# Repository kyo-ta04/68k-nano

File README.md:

# 68k nano

A minimal single-board computer based on the venerable ["Texas Cockroach"](https://youtu.be/UaHtGf4aRLs?t=2074)
Motorola 68000 16/32-bit microprocessor.

## Schematic, PCB
Schematic : [KiCanvas](https://kicanvas.org/?github=https%3A%2F%2Fgithub.com%2Fkyo-ta04%2F68k-nano%2Fblob%2FDevelop%2F68000sbc.kicad_sch) , [PDF](./68000sbc_sch.pdf)  
PCB : [KiCanvas](https://kicanvas.org/?github=https%3A%2F%2Fgithub.com%2Fkyo-ta04%2F68k-nano%2Fblob%2FDevelop%2F68000sbc.kicad_pcb) , 
[Gerber files](./production/)  

** I added the schematic and PCB using KiCad 9.0.4  -  kyo-ta04(@DragonballEZ) 15-Sep-2025  

## Features

- 68HC000 processor running at 12MHz
- 1MB RAM
- 64KB ROM
- 16550 UART providing a 5V FTDI serial port
- 44-pin IDE connector for CompactFlash card adapter
- Connector for SparkFun DS3234 real-time clock
- Only two 74HC glue logic chips required

This might be capable of running uClinux, but I haven't tried it!

## Hardware

The 68k nano hardware is simple and straightforward. It can be built on a
breadboard (though there may be stability issues at higher clock speeds).

### Memory map

Due to the minimal address decoding circuitry, accessing certain memory regions
will cause multiple devices to be selected. This should be avoided.

```
$000000-0xFFFF     ROM (repeats 16 times)
$100000-1FFFFF  X  Forbidden (multiple devices selected)
$200000-2FFFFF     ROM (mirror of $000000-0FFFFF)
$300000-$7FFFF  X  Forbidden (multiple devices selected)
$800000-8FFFFF     Open bus (available for expansion)
$900000-9xxxxF     CompactFlash card
$A00000-AxxxxF     UART
$B00000-BFFFFF  X  Forbidden (multiple devices selected)
$C00000-CFFFFF     RAM
$D00000-DFFFFF  X  Forbidden (multiple devices selected)
$E00000-EFFFFF     RAM (mirror of $C00000-CFFFFF)
$F00000-FFFFFF  X  Forbidden (multiple devices selected)
```

This is summarized with the following equations:

```
/ROMSEL  = /A23
/RAMSEL  =  A22
/UARTSEL =  A23 * /A22 * A21
/CARDSEL =  A20
```

### I/O

The 16550's modem control lines are used as a bit-banged SPI interface. A 7-pin
header is provided for [SparkFun's "DeadOn" DS3234 real-time clock board](https://www.sparkfun.com/products/10160).
Access to SPI is therefore achieved via the 16550's Modem Control Register and Line
Status Register.

A 2mm pitch 44-pin IDE connector is provided for storage devices. This is
intended for CompactFlash card adapters (operating in 16-bit True IDE mode) but
may also work with parallel ATA hard disks. (not tested)

### Interrupts

All interrupt sources are routed through the 16550. All 16550 interrupts invoke
the level 1 autovector (vector offset `$064`) and it is up to the software to
determine the source of the interrupt.

### Building it

`bom.txt` contains a bill of materials. As of this writing (July 2020), all
components are available from major distributors like [Mouser](https://mouser.com)
and [Jameco](https://jameco.com). If purchasing 68000s from eBay, note that [vintage
ICs are a common target of counterfeiters](https://medium.com/supplyframe-hardware/the-underground-parts-store-identifying-counterfeit-computer-chips-3020adbb01f7).
For this project I used [Toshiba TMP68HC000P-12 chips from Jameco](https://www.jameco.com/shop/ProductDisplay?catalogId=10001&langId=-1&storeId=10001&productId=2288039) and
they work just fine.

All parts are through-hole for that extra vintage feel. Note that some of the
decoupling capacitors (C4, C5, C6, C8, and C10) are underneath ICs, so open-frame
IC sockets are required. Large IC sockets can also be expensive (_especially_
DIP-64 sockets!) so a cheaper alternative is to use [breakaway SIP 0.1" machine-pin
headers](https://www.amazon.com/dp/B0187LTEX2/ref=cm_sw_em_r_mt_dp_U_M5IbFbVJ3NVDH).

Due to the spacing of the chips, Textool ZIF sockets won't fit. For the ROMs
U5 and U7, [Aries 28-526-10 low-profile ZIF sockets](https://www.jameco.com/shop/ProductDisplay?catalogId=10001&langId=-1&storeId=10001&productId=102745) will fit,
but _barely_. The release latch may scrape against the RAM IC to its north,
but I've found that it's not a huge deal.

You can use either a full-can or half-can oscillator for X1. Note that if using
an oscillator with a frequency other than 12 MHz, you'll have to update the `F_CPU`
value in the Makefile. (see below) Also note that, if using a 68HC000, the minimum
clock frequency is 4 MHz.

The 44-pin IDE header accepts a CompactFlash adapter board such as [this one](https://www.amazon.com/gp/product/B07Y2MTS13), available from Amazon and other vendors.

## Software

This project uses the [vasm](http://sun.hasenbraten.de/vasm/) assembler and a
standard Makefile. Python 3 and [PySerial](https://pythonhosted.org/pyserial/)
are also required to upload programs to the computer via the serial port. The
Makefile also contains rules for burning ROM images to AT28C256 EEPROMs using
[minipro](https://gitlab.com/DavidGriffith/minipro/) if you have a [TL866II+](https://www.jameco.com/shop/ProductDisplay?catalogId=10001&langId=-1&storeId=10001&productId=2297823)
programmer. (If you don't have a chip programmer, you should get a TL866II+, they
are reasonably priced and available from a number of vendors.)

### Building it

Running `make rom` will build the ROM image and split it into "odd" and "even"
halves, `rom-l.bin` and `rom-u.bin`. Each file should be 32,768 bytes exactly.
Running `make burnrom` will write these files to a pair of AT28C256 EEPROMs
using minipro.

**Note:** if using an oscillator with a frequency other than 12 MHz, change the
value of `F_CPU` appropriately in the Makefile.

The `BAUD` variable in the Makefile sets the baud rate of the serial interface.
Use the included script `baudrate.py` to determine which baud rates are usable
with a given oscillator frequency.

### ROM features

The ROM is fairly minimal--it's closer to a bootloader than an operating system.
It supports loading programs from the root directory of a FAT16-formatted
CompactFlash card and some basic debugging functionality. It also provides a
small set of system calls for I/O to simplify application programs.

The power-up process is as follows:
- Initialize serial port to 57600 baud, 8 data bits, no parity, 1 stop bit.
- Test RAM. If a RAM failure occurs, the failed address is written to the serial
port and the Status LED flashes rapidly. (This is prone to failure when running
on a breadboard at higher clock speeds.)
- Check for the real-time clock module. If found, print the current date and
time to the serial port.
- Check for a CompactFlash card, and attempt to mount the first partition if it
is FAT16-formatted.
- If the "ENTER" pushbutton is NOT held down:
  - If a valid card is inserted, check for a file in the root directory named
    `STARTUP.BIN`. If found, load it into RAM and execute it.
  - If `STARTUP.BIN` was not loaded, enter an interactive command shell.
- If the "ENTER" pushbutton is held down, enter the interactive command shell
  and bypass execution of `STARTUP.BIN`.

Example startup sequence (without `STARTUP.BIN`):
```
68K NANO - ROM VERSION 00009900 (20200708)
(C) 2020 MATT SARNOFF (MSARNOFF.ORG)
TESTING RAM...PASSED

RAM: 1,048,576 BYTES
ROM: 65,536 BYTES
CPU: 12,000,000 HZ
TIME IS 2020-07-07 19:14:36
CARD DETECTED: 250,608 KB 'NO NAME    '
CANNOT LOAD STARTUP.BIN - FILE NOT FOUND

TYPE ? [ENTER] FOR HELP.
>
```

### Command shell

If `STARTUP.BIN` was not loaded, an interactive command shell is available via
the serial port. (57600 baud, 8 data bits, no parity, 1 stop bit). Type `?` and
press Enter for a list of supported commands. They are summarized briefly here.
Note that commands and filenames are _case-insensitive_.

- `.L` - list files in the root directory of the CompactFlash card. Long filenames
  and hidden files are not displayed.
- `.I` - print low-level information about the filesystem on the CompactFlash card.
- `.P file` - print the contents of the file named `file` in the root directory
  of the CompactFlash card as ASCII text.
- `.H file` - print the contenxt of the file named `file` in the root directory
  of the CompactFlash card as a hexdump.
- `.T` - print the current date and time as reported by the real-time clock module.
- `.T YYYYMMDDWWhhmmss` - set the current date and time. The new date/time should
  be expressed as a string of 16 decimal digits with no separators. `WW` should
  be a 2-digit weekday between `01` and `07` inclusive. You can obtain the
  current date/time in this format with the Unix command `date "+%Y%m%d0%u%H%M%S"`.
- `.D` - enter the debugger.
- `file` - any other command is interpreted as a filename to be loaded from the
  root directory of the CompactFlash card and executed. Unlike MS-DOS, the file
  extension _is_ required. e.g. to execute the file named _foo.bin_, enter `FOO.BIN`.
  (`FOO` will attempt to load a file named _foo_ with no extension).

### Serial loader

A break condition on the serial input line enters the serial loader, allowing
programs to be uploaded to RAM from a host computer. The Python script `serload.py`
and the Makefile rules `make load` and `make run` take care of this.

### Debugging

A hardware exception causes a transfer into a basic debugger. The Status LED
flashes rapidly and a register dump is printed to the serial port:

```
*ILLEGAL INSTRUCTION
D0=00000064  D1=0000000A  D2=00000038  D3=00000009
D4=00000000  D5=00000000  D6=00000000  D7=00000000
A0=00E0003C  A1=00001D40  A2=00000000  A3=00F00000
A4=00000000  A5=00000000  A6=000001E2  A7=00EFFFFA
SR=-S0--Z--  PC=00001D3A              USP=7F7EFFDF

[A]BORT/[C]ONTINUE/[S]TEP?
```

Supported commands are:
- `a` - abort execution and return to system.
- `c` - (attempt to) continue execution. (the Trace bit is cleared)
- `s` - set the Trace bit and single-step.

`TRAP #15` is treated as a breakpoint instruction that also enters the debugger.

### API

See `API.md` for a detailed description of the system calls provided by the ROM
API and guidelines for application programs.

## Known issues and shortcomings

- ROM is always present at the bottom of the address space, so the exception
  vectors cannot be overridden by application code.
- Interrupt handling is a hack, since all interrupt sources go through the 16550.
- Address decoding leaves little room for expansion.
- System calls should set the condition codes to simplify application code.

## Future directions

This is a small-scale project. I'm thinking about desiging a larger 68000 board
in the future, so I probably won't continue working on this one. Here are some
project ideas that I won't have time to tackle, but you're welcome to:

- Running an existing 68k monitor like [TUTOR](http://www.easy68k.com/paulrsm/mecb/mecb.htm)
  or [zBug](http://www.kswichit.com/68k/68k.html).
- Running a language like [EhBASIC](https://github.com/jefftranter/68000/tree/master/ehbasic) or a Forth.
- Adding FAT16 write support.
- Booting [uClinux](https://www.bigmessowires.com/2014/11/17/68-katy-68000-linux-on-a-solderless-breadboard/) like Steve Chamberlin did with [68 Katy](https://www.bigmessowires.com/category/68katy/).
- Using the DS3234 real-time clock's SQW output to generate a periodic interrupt.
  (likely necessary for uClinux)

## About

Open hardware, released under the terms of the 3-clause BSD license.

Copyright 2020 Matt Sarnoff.

http://twitter.com/txsector

http://msarnoff.org

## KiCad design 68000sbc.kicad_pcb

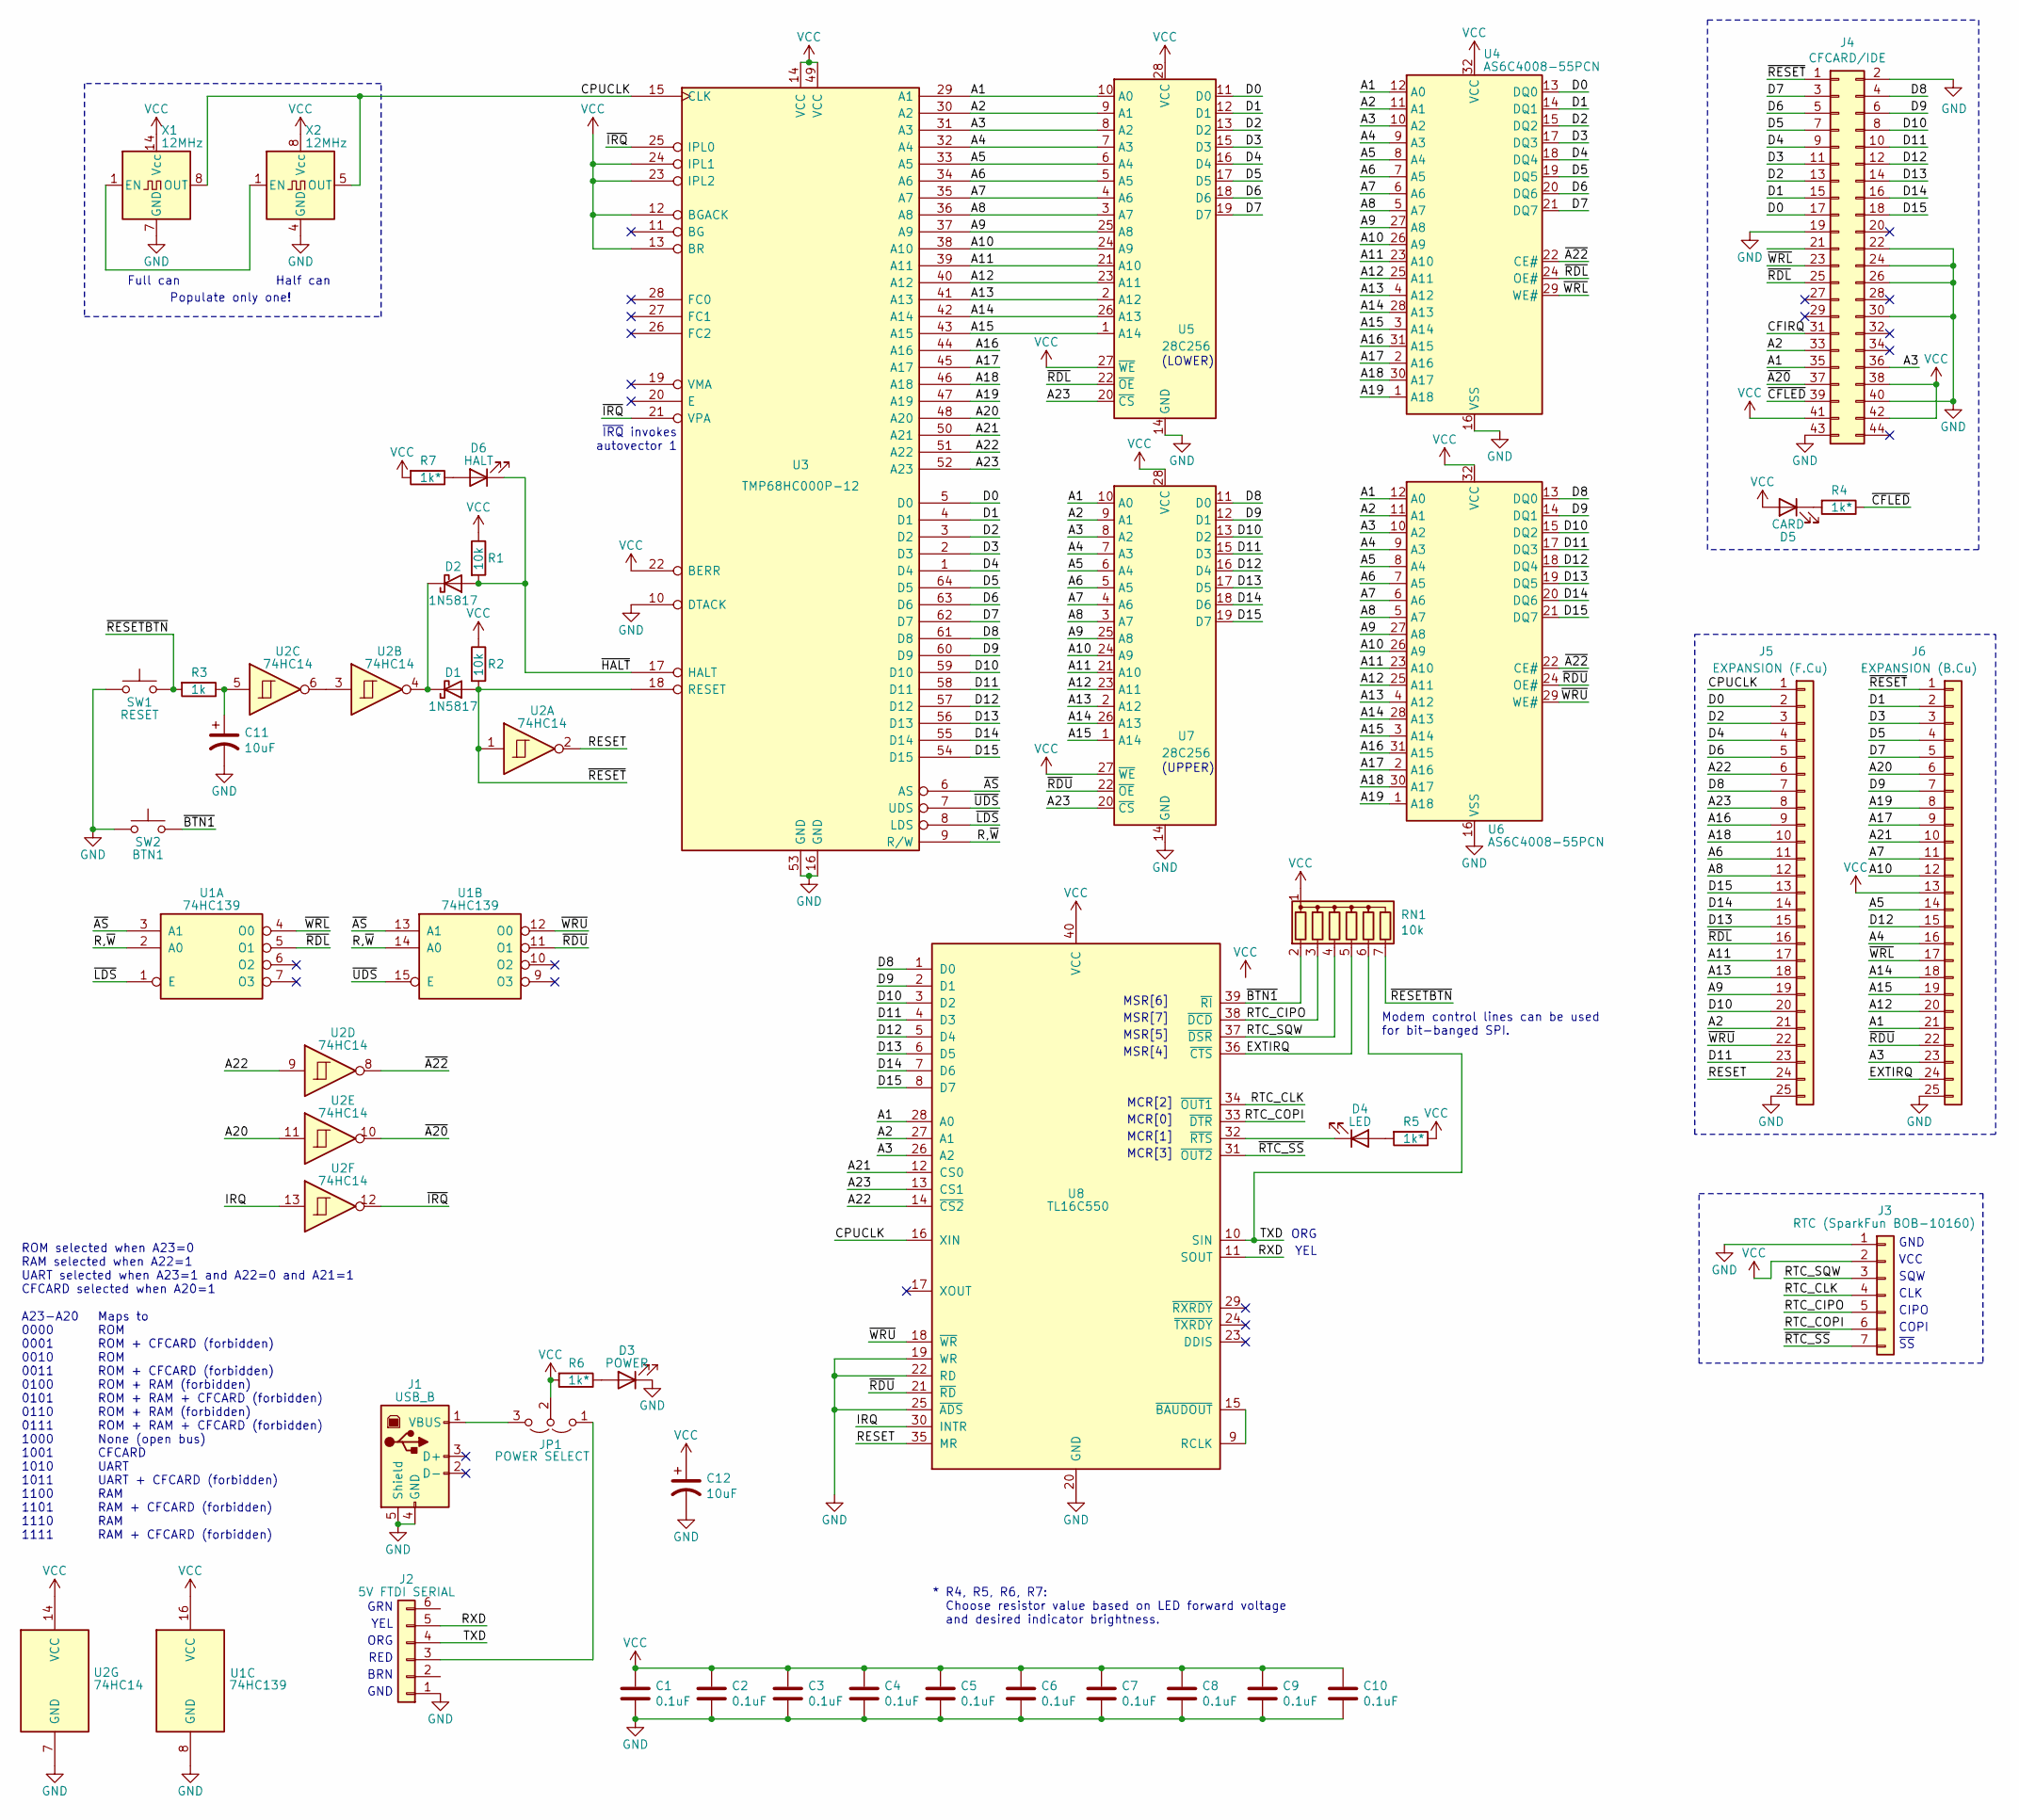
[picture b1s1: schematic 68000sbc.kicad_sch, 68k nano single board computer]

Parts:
C1, C2, C3, C4, C5, C6, C7, C8, C9, C10: 0.1uF; C_Rect_L7.0mm_W2.0mm_P5.00mm
C11, C12: 10uF; CP_Radial_D5.0mm_P2.50mm
D1, D2: 1N5817; D_DO-35_SOD27_P7.62mm_Horizontal
D3: POWER; LED_D5.0mm
D4: LED; LED_D5.0mm
D5: CARD; LED_D5.0mm
D6: HALT; LED_D5.0mm
J1: USB_B; USB_B_OST_USB-B1HSxx_Horizontal
J2: 5V FTDI SERIAL; PinHeader_1x06_P2.54mm_Horizontal
J3: RTC (SparkFun BOB-10160); PinHeader_1x07_P2.54mm_Vertical
J4: CFCARD/IDE; PinHeader_2x22_P2.00mm_Vertical
J5: EXPANSION (F.Cu); PadRow_1x25_P2.54mm
J6: EXPANSION (B.Cu); PadRow_1x25_P2.54mm
JP1: POWER SELECT; PinHeader_1x03_P2.54mm_Vertical
R1, R2: 10k; R_Axial_DIN0204_L3.6mm_D1.6mm_P7.62mm_Horizontal
R3: 1k; R_Axial_DIN0204_L3.6mm_D1.6mm_P7.62mm_Horizontal
R4, R5, R6, R7: 1k*; R_Axial_DIN0204_L3.6mm_D1.6mm_P7.62mm_Horizontal
RN1: 10k; R_Array_SIP7
SW1: RESET; SW_PUSH_6mm
SW2: BTN1; SW_PUSH_6mm
U1: 74HC139; DIP-16_W7.62mm_Socket
U2: 74HC14; DIP-14_W7.62mm_Socket
U3: TMP68HC000P-12; DIP-64_W22.86mm_Socket
U4, U6: AS6C4008-55PCN; DIP-32_W15.24mm_Socket
U5, U7: 28C256; DIP-28_W15.24mm_Socket
U8: TL16C550; DIP-40_W15.24mm_Socket
X1: 12MHz; Oscillator_DIP-14
X2: 12MHz; Oscillator_DIP-8

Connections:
/A1: J4.35, J6.21, U3.29 (A1), U4.12 (A0), U5.10 (A0), U6.12 (A0), U7.10 (A0), U8.28 (A0)
/A2: J4.33, J5.21, U3.30 (A2), U4.11 (A1), U5.9 (A1), U6.11 (A1), U7.9 (A1), U8.27 (A1)
/A3: J4.36, J6.23, U3.31 (A3), U4.10 (A2), U5.8 (A2), U6.10 (A2), U7.8 (A2), U8.26 (A2)
/A4: J6.16, U3.32 (A4), U4.9 (A3), U5.7 (A3), U6.9 (A3), U7.7 (A3)
/A5: J6.14, U3.33 (A5), U4.8 (A4), U5.6 (A4), U6.8 (A4), U7.6 (A4)
/A6: J5.11, U3.34 (A6), U4.7 (A5), U5.5 (A5), U6.7 (A5), U7.5 (A5)
/A7: J6.11, U3.35 (A7), U4.6 (A6), U5.4 (A6), U6.6 (A6), U7.4 (A6)
/A8: J5.12, U3.36 (A8), U4.5 (A7), U5.3 (A7), U6.5 (A7), U7.3 (A7)
/A9: J5.19, U3.37 (A9), U4.27 (A8), U5.25 (A8), U6.27 (A8), U7.25 (A8)
/A10: J6.12, U3.38 (A10), U4.26 (A9), U5.24 (A9), U6.26 (A9), U7.24 (A9)
/A11: J5.17, U3.39 (A11), U4.23 (A10), U5.21 (A10), U6.23 (A10), U7.21 (A10)
/A12: J6.20, U3.40 (A12), U4.25 (A11), U5.23 (A11), U6.25 (A11), U7.23 (A11)
/A13: J5.18, U3.41 (A13), U4.4 (A12), U5.2 (A12), U6.4 (A12), U7.2 (A12)
/A14: J6.18, U3.42 (A14), U4.28 (A13), U5.26 (A13), U6.28 (A13), U7.26 (A13)
/A15: J6.19, U3.43 (A15), U4.3 (A14), U5.1 (A14), U6.3 (A14), U7.1 (A14)
/A16: J5.9, U3.44 (A16), U4.31 (A15), U6.31 (A15)
/A17: J6.9, U3.45 (A17), U4.2 (A16), U6.2 (A16)
/A18: J5.10, U3.46 (A18), U4.30 (A17), U6.30 (A17)
/A19: J6.8, U3.47 (A19), U4.1 (A18), U6.1 (A18)
/A20: J6.6, U2.11, U3.48 (A20)
/A21: J6.10, U3.50 (A21), U8.12 (CS0)
/A22: J5.6, U2.9, U3.51 (A22), U8.14 (~CS2)
/A23: J5.8, U3.52 (A23), U5.20 (~CS), U7.20 (~CS), U8.13 (CS1)
/CFIRQ: J4.31
/CPUCLK: J5.1, U3.15 (CLK), U8.16 (XIN), X1.8 (OUT), X2.5 (OUT)
/D0: J4.17, J5.2, U3.5 (D0), U4.13 (DQ0), U5.11 (D0)
/D1: J4.15, J6.2, U3.4 (D1), U4.14 (DQ1), U5.12 (D1)
/D2: J4.13, J5.3, U3.3 (D2), U4.15 (DQ2), U5.13 (D2)
/D3: J4.11, J6.3, U3.2 (D3), U4.17 (DQ3), U5.15 (D3)
/D4: J4.9, J5.4, U3.1 (D4), U4.18 (DQ4), U5.16 (D4)
/D5: J4.7, J6.4, U3.64 (D5), U4.19 (DQ5), U5.17 (D5)
/D6: J4.5, J5.5, U3.63 (D6), U4.20 (DQ6), U5.18 (D6)
/D7: J4.3, J6.5, U3.62 (D7), U4.21 (DQ7), U5.19 (D7)
/D8: J4.4, J5.7, U3.61 (D8), U6.13 (DQ0), U7.11 (D0), U8.1 (D0)
/D9: J4.6, J6.7, U3.60 (D9), U6.14 (DQ1), U7.12 (D1), U8.2 (D1)
/D10: J4.8, J5.20, U3.59 (D10), U6.15 (DQ2), U7.13 (D2), U8.3 (D2)
/D11: J4.10, J5.23, U3.58 (D11), U6.17 (DQ3), U7.15 (D3), U8.4 (D3)
/D12: J4.12, J6.15, U3.57 (D12), U6.18 (DQ4), U7.16 (D4), U8.5 (D4)
/D13: J4.14, J5.15, U3.56 (D13), U6.19 (DQ5), U7.17 (D5), U8.6 (D5)
/D14: J4.16, J5.14, U3.55 (D14), U6.20 (DQ6), U7.18 (D6), U8.7 (D6)
/D15: J4.18, J5.13, U3.54 (D15), U6.21 (DQ7), U7.19 (D7), U8.8 (D7)
/EXTIRQ: J6.24, RN1.5 (R4), U8.36 (~CTS)
/IRQ: U2.13, U8.30 (INTR)
/R,~W: U1.2 (A0), U1.14 (A0), U3.9 (R/W)
/RESET: J5.24, U2.2, U8.35 (MR)
/RTC_CIPO: J3.5, RN1.3 (R2), U8.38 (~DCD)
/RTC_CLK: J3.4, U8.34 (~OUT1)
/RTC_COPI: J3.6, U8.33 (~DTR)
/RTC_SQW: J3.3, RN1.4 (R3), U8.37 (~DSR)
/RXD: J2.5, U8.11 (SOUT)
/TXD: J2.4, RN1.6 (R5), U8.10 (SIN)
/~A20: J4.37, U2.10
/~A22: U2.8, U4.22 (CE#), U6.22 (CE#)
/~AS: U1.3 (A1), U1.13 (A1), U3.6 (AS)
/~BTN1: RN1.2 (R1), SW2.2, U8.39 (~RI)
/~CFLED: J4.39, R4.1
/~HALT: D2.2 (A), D6.1 (K), R1.2, U3.17 (HALT)
/~IRQ: U2.12, U3.21 (VPA), U3.25 (IPL0)
/~LDS: U1.1 (E), U3.8 (LDS)
/~RDL: J4.25, J5.16, U1.5 (O1), U4.24 (OE#), U5.22 (~OE)
/~RDU: J6.22, U1.11 (O1), U6.24 (OE#), U7.22 (~OE), U8.21 (~RD)
/~RESETBTN: R3.2, RN1.7 (R6), SW1.2
/~RESET: D1.2 (A), J4.1, J6.1, R2.2, U2.1, U3.18 (RESET)
/~RTC_SS: J3.7, U8.31 (~OUT2)
/~UDS: U1.15 (E), U3.7 (UDS)
/~WRL: J4.23, J6.17, U1.4 (O0), U4.29 (WE#)
/~WRU: J5.22, U1.12 (O0), U6.29 (WE#), U8.18 (~WR)
GND: C1.2, C2.2, C3.2, C4.2, C5.2, C6.2, C7.2, C8.2, C9.2, C10.2, C11.2, C12.2, D3.1 (K), J1.4 (GND), J1.5 (Shield), J2.1, J3.1, J4.2, J4.19, J4.22, J4.24, J4.26, J4.30, J4.40, J4.43, J5.25, J6.25, SW1.1, SW2.1, U1.8 (GND), U2.7 (GND), U3.10 (DTACK), U3.16 (GND), U3.53 (GND), U4.16 (VSS), U5.14 (GND), U6.16 (VSS), U7.14 (GND), U8.19 (WR), U8.20 (GND), U8.22 (RD), U8.25 (~ADS), X1.7 (GND), X2.4 (GND)
unnamed: C11.1, R3.1, U2.5
unnamed: D1.1 (K), D2.1 (K), U2.4
unnamed: D3.2 (A), R6.1
unnamed: D4.1 (K), U8.32 (~RTS)
unnamed: D4.2 (A), R5.2
unnamed: D5.1 (K), R4.2
unnamed: D6.2 (A), R7.1
unnamed: J1.1 (VBUS), JP1.3 (B)
unnamed: J2.3, JP1.1 (A)
unnamed: U2.3, U2.6
unnamed: U8.9 (RCLK), U8.15 (~BAUDOUT)
unnamed: X1.1 (EN), X2.1 (EN)
VCC: C1.1, C2.1, C3.1, C4.1, C5.1, C6.1, C7.1, C8.1, C9.1, C10.1, C12.1, D5.2 (A), J3.2, J4.38, J4.41, J4.42, J6.13, JP1.2 (C), R1.1, R2.1, R5.1, R6.2, R7.2, RN1.1 (common), U1.16 (VCC), U2.14 (VCC), U3.12 (BGACK), U3.13 (BR), U3.14 (VCC), U3.22 (BERR), U3.23 (IPL2), U3.24 (IPL1), U3.49 (VCC), U4.32 (VCC), U5.27 (~WE), U5.28 (VCC), U6.32 (VCC), U7.27 (~WE), U7.28 (VCC), U8.40 (VCC), X1.14 (Vcc), X2.8 (Vcc)

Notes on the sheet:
Populate only one!
MSR[5]
ROM selected when A23=0 RAM selected when A22=1 UART selected when A23=1 and A22=0 and A21=1 CFCARD selected when A20=1
CLK
CIPO
RED
ORG
MCR[1]
MSR[7]
Half can
Modem control lines can be used for bit-banged SPI.
(LOWER)
VCC
MSR[4]
~{IRQ} invokes autovector 1
GRN
Full can
(UPPER)
MSR[6]
YEL
Maps to ROM ROM + CFCARD (forbidden) ROM ROM + CFCARD (forbidden) ROM + RAM (forbidden) ROM + RAM + CFCARD (forbidden) ROM + RAM (forbidden) ROM + RAM + CFCARD (forbidden) None (open bus) CFCARD UART UART + CFCARD (forbidden) RAM RAM + CFCARD (forbidden) RAM RAM + CFCARD (forbidden)
GND
A23-A20 0000 0001 0010 0011 0100 0101 0110 0111 1000 1001 1010 1011 1100 1101 1110 1111
SQW
MCR[3]
MCR[2]
MCR[0]
BRN
COPI
* R4, R5, R6, R7: Choose resistor value based on LED forward voltage and desired indicator brightness.
~{SS}

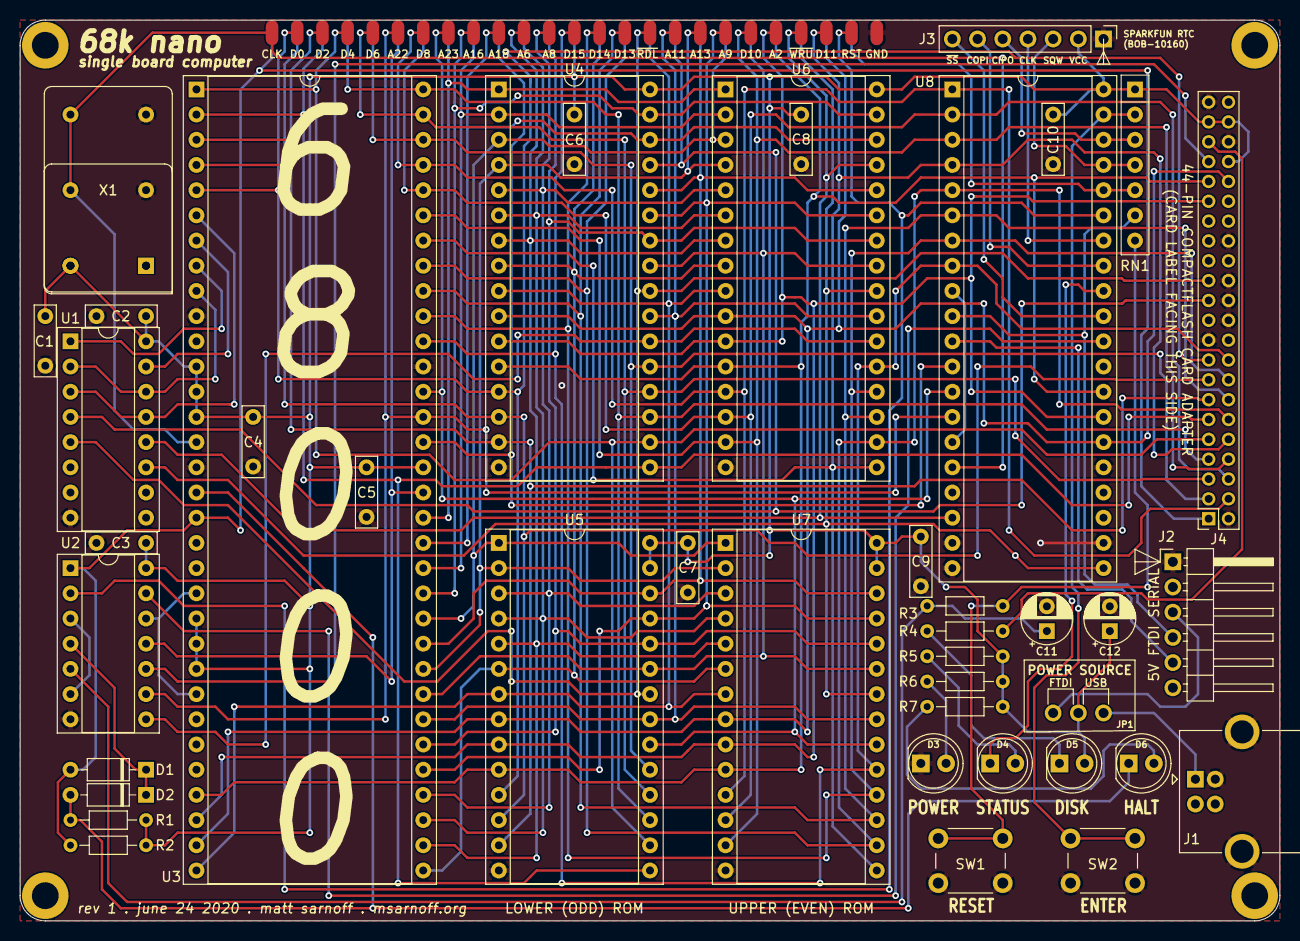
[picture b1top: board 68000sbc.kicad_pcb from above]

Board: 2 copper layers, 127.0 x 90.8 mm, 45 parts (1 on the bottom side), 80 nets.

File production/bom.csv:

Designator,Footprint,Quantity,Value,LCSC Part #
"C1, C10, C2, C3, C4, C5, C6, C7, C8, C9",C_Rect_L7.0mm_W2.0mm_P5.00mm,10,0.1uF,
"C11, C12",CP_Radial_D5.0mm_P2.50mm,2,10uF,
"D1, D2",D_DO-35_SOD27_P7.62mm_Horizontal,2,1N5817,
D3,LED_D5.0mm,1,POWER,
D4,LED_D5.0mm,1,LED,
D5,LED_D5.0mm,1,CARD,
D6,LED_D5.0mm,1,HALT,
J1,USB_B_OST_USB-B1HSxx_Horizontal,1,USB_B,
J2,PinHeader_1x06_P2.54mm_Horizontal,1,5V FTDI SERIAL,
J3,PinHeader_1x07_P2.54mm_Vertical,1,RTC (SparkFun BOB-10160),
J4,PinHeader_2x22_P2.00mm_Vertical,1,CFCARD/IDE,
J5,PadRow_1x25_P2.54mm,1,EXPANSION (F.Cu),
J6,PadRow_1x25_P2.54mm,1,EXPANSION (B.Cu),
JP1,PinHeader_1x03_P2.54mm_Vertical,1,POWER SELECT,
"R1, R2",R_Axial_DIN0204_L3.6mm_D1.6mm_P7.62mm_Horizontal,2,10k,
R3,R_Axial_DIN0204_L3.6mm_D1.6mm_P7.62mm_Horizontal,1,1k,
"R4, R5, R6, R7",R_Axial_DIN0204_L3.6mm_D1.6mm_P7.62mm_Horizontal,4,1k*,
RN1,R_Array_SIP7,1,10k,
SW1,SW_PUSH_6mm,1,RESET,
SW2,SW_PUSH_6mm,1,BTN1,
U1,DIP-16_W7.62mm_Socket,1,74HC139,
U2,DIP-14_W7.62mm_Socket,1,74HC14,
U3,DIP-64_W22.86mm_Socket,1,TMP68HC000P-12,
"U4, U6",DIP-32_W15.24mm_Socket,2,AS6C4008-55PCN,
"U5, U7",DIP-28_W15.24mm_Socket,2,28C256,
U8,DIP-40_W15.24mm_Socket,1,TL16C550,
X1,Oscillator_DIP-14,1,12MHz,
X2,Oscillator_DIP-8,1,12MHz,

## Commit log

2025-09-14 U3,C11,C12をNew_Libraryへ移動
2025-09-14 ファブリケーション
2025-09-15 回路図、PCB,ガーバー追加
2025-09-15 README.md 修正
2025-09-15 68000sbc.pro,sch削除
2025-09-15 .gitignore 修正
